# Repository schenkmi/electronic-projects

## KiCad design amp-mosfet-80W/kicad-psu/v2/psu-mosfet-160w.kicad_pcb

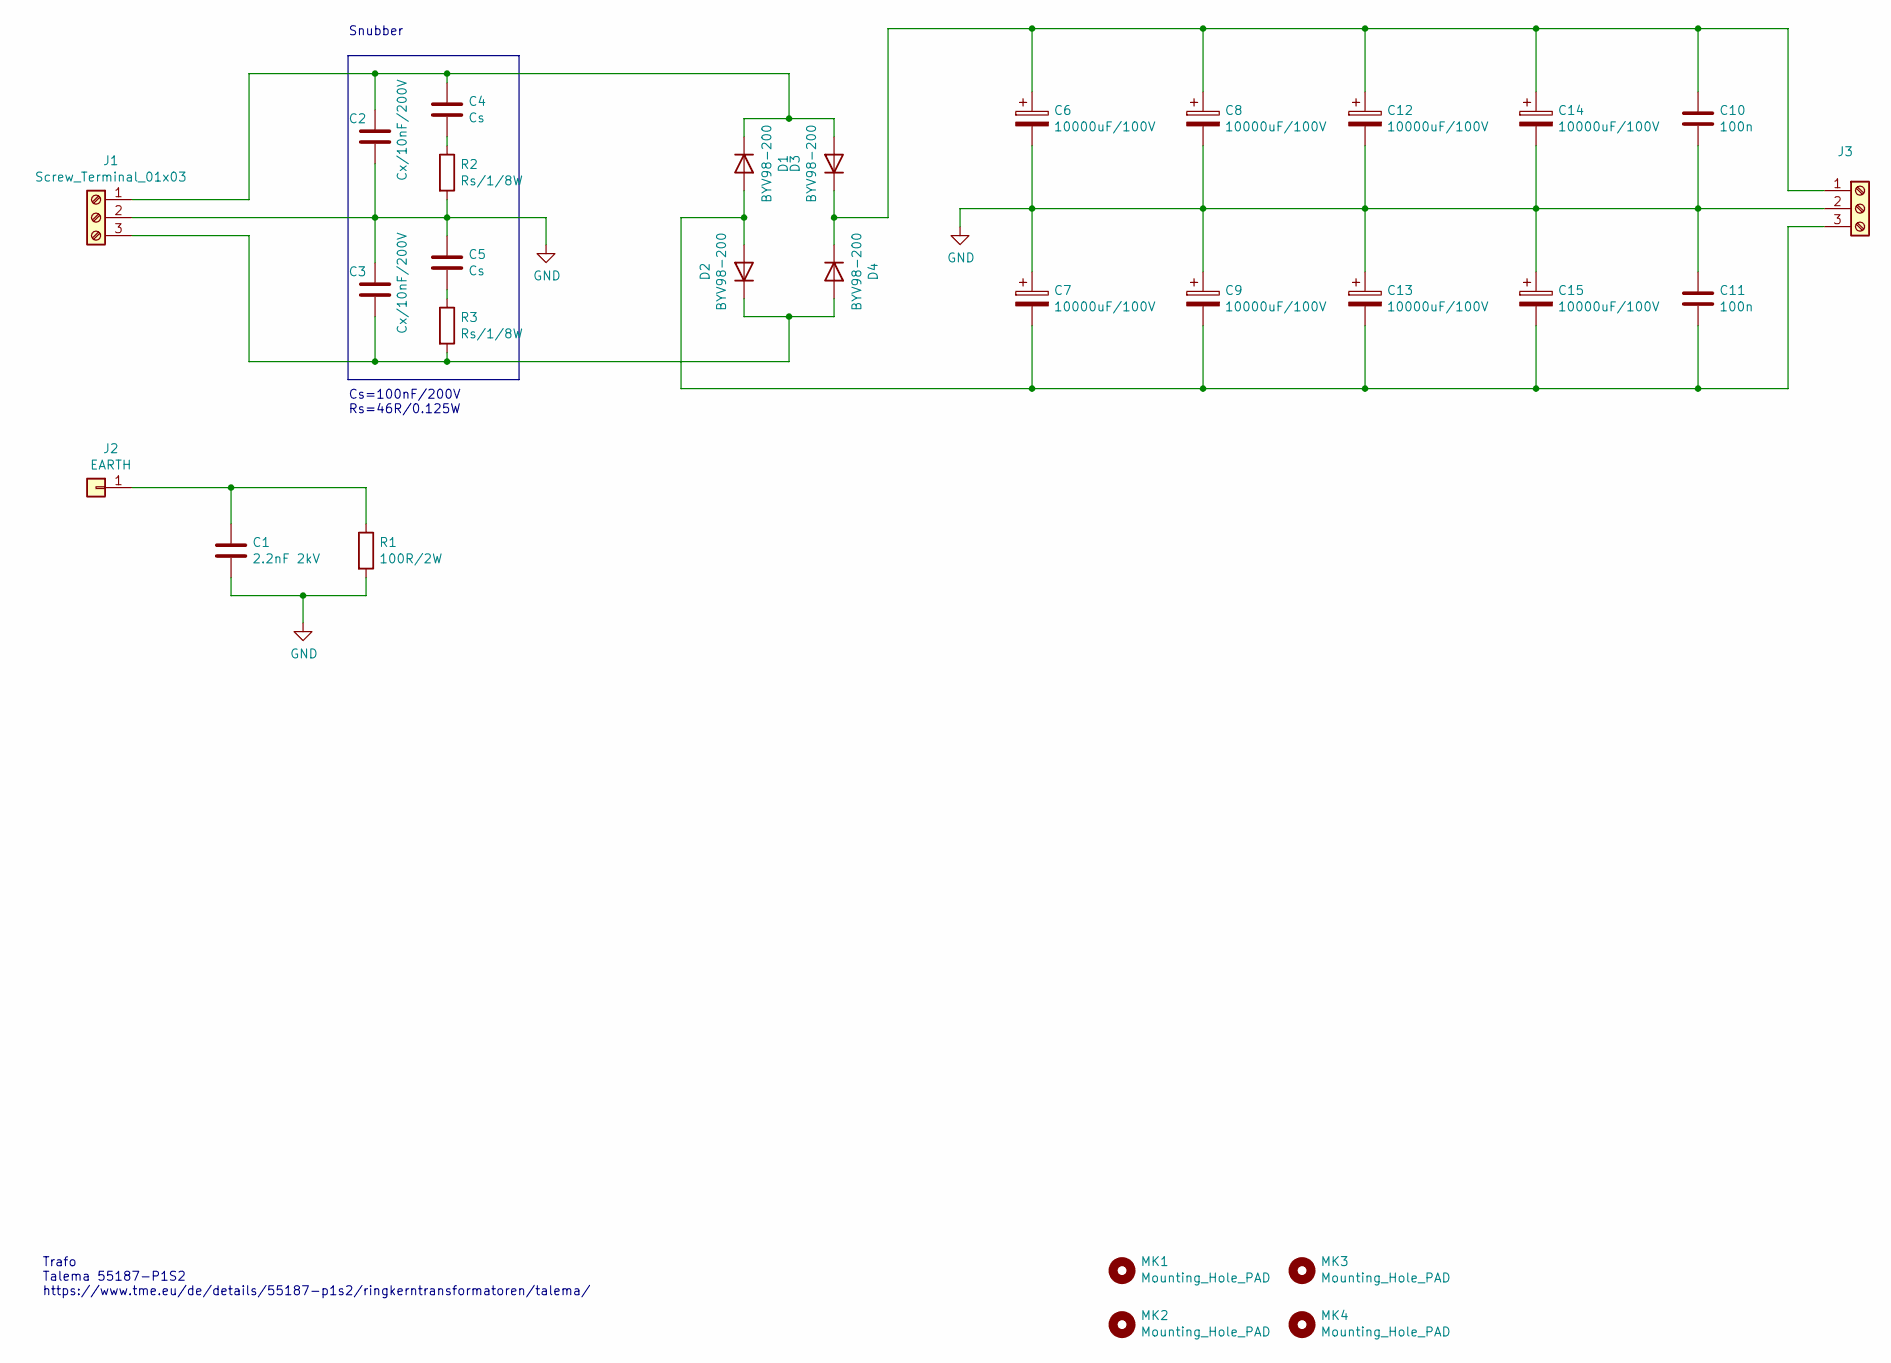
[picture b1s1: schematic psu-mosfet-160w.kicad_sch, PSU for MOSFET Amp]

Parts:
C1: 2.2nF 2kV; C_Rect_L18.0mm_W5.0mm_P15.00mm_FKS3_FKP3
C2, C3: Cx/10nF/200V; C_0805_2012Metric_Pad1.18x1.45mm_HandSolder
C4, C5: Cs; C_1206_3216Metric_Pad1.33x1.80mm_HandSolder
C6, C7, C8, C9, C12, C13, C14, C15: 10000uF/100V; CP_Radial_D40.0mm_P10.00mm_SnapIn
C10, C11: 100n; C_Rect_L7.2mm_W2.5mm_P5.00mm_FKS2_FKP2_MKS2_MKP2
D1, D2, D3, D4: BYV98-200; SOD64-10
J1, J3: Screw_Terminal_01x03; TerminalBlock_RND_205-00013_1x03_P5.00mm_Horizontal
J2: EARTH; Pin_D1.3mm_L11.0mm
MK1, MK2, MK3, MK4: Mounting_Hole_PAD; MountingHole_3.2mm_M3
R1: 100R/2W; R_Axial_DIN0414_L11.9mm_D4.5mm_P15.24mm_Horizontal
R2, R3: Rs/1/8W; R_0805_2012Metric_Pad1.20x1.40mm_HandSolder

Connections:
GND: C1.2, C2.2, C3.1, C5.1, C6.2, C7.1, C8.2, C9.1, C10.2, C11.1, C12.2, C13.1, C14.2, C15.1, J1.2, J3.2, R1.2, R2.2
unnamed: C1.1, J2.1, R1.1
unnamed: C2.1, C4.1, D1.1 (K), D3.2 (A), J1.1
unnamed: C3.2, D2.1 (K), D4.2 (A), J1.3, R3.2
unnamed: C4.2, R2.1
unnamed: C5.2, R3.1
unnamed: C6.1, C8.1, C10.1, C12.1, C14.1, D3.1 (K), D4.1 (K), J3.1
unnamed: C7.2, C9.2, C11.2, C13.2, C15.2, D1.2 (A), D2.2 (A), J3.3

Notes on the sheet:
Snubber
Trafo Talema 55187-P1S2 https://www.tme.eu/de/details/55187-p1s2/ringkerntransformatoren/talema/
Cs=100nF/200V Rs=46R/0.125W

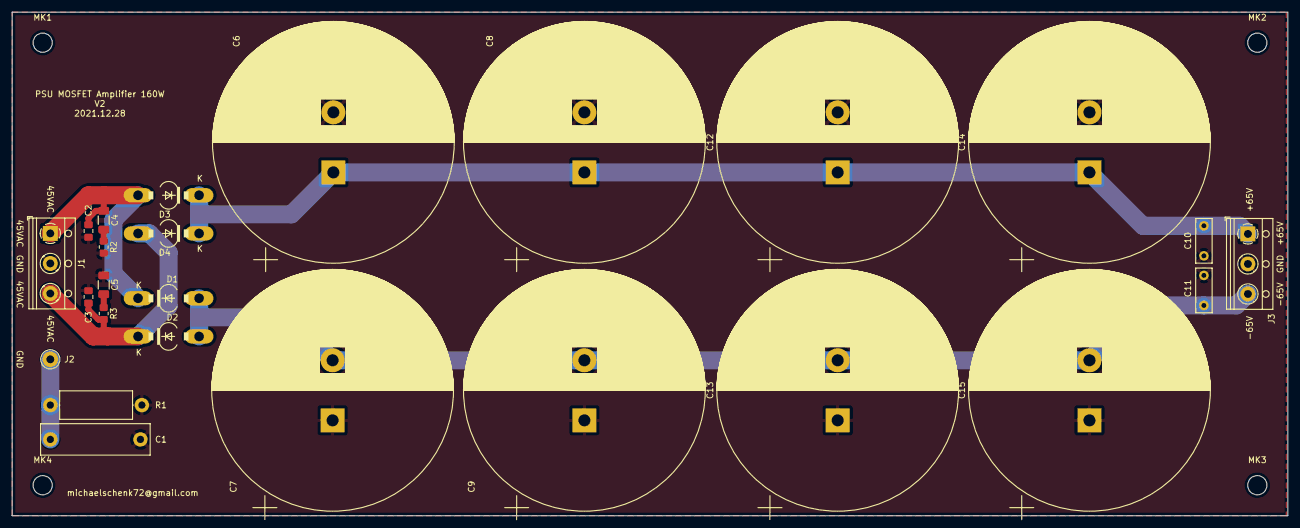
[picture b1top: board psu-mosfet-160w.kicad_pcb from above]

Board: 2 copper layers, 212.3 x 83.8 mm, 29 parts (0 on the bottom side), 8 nets.

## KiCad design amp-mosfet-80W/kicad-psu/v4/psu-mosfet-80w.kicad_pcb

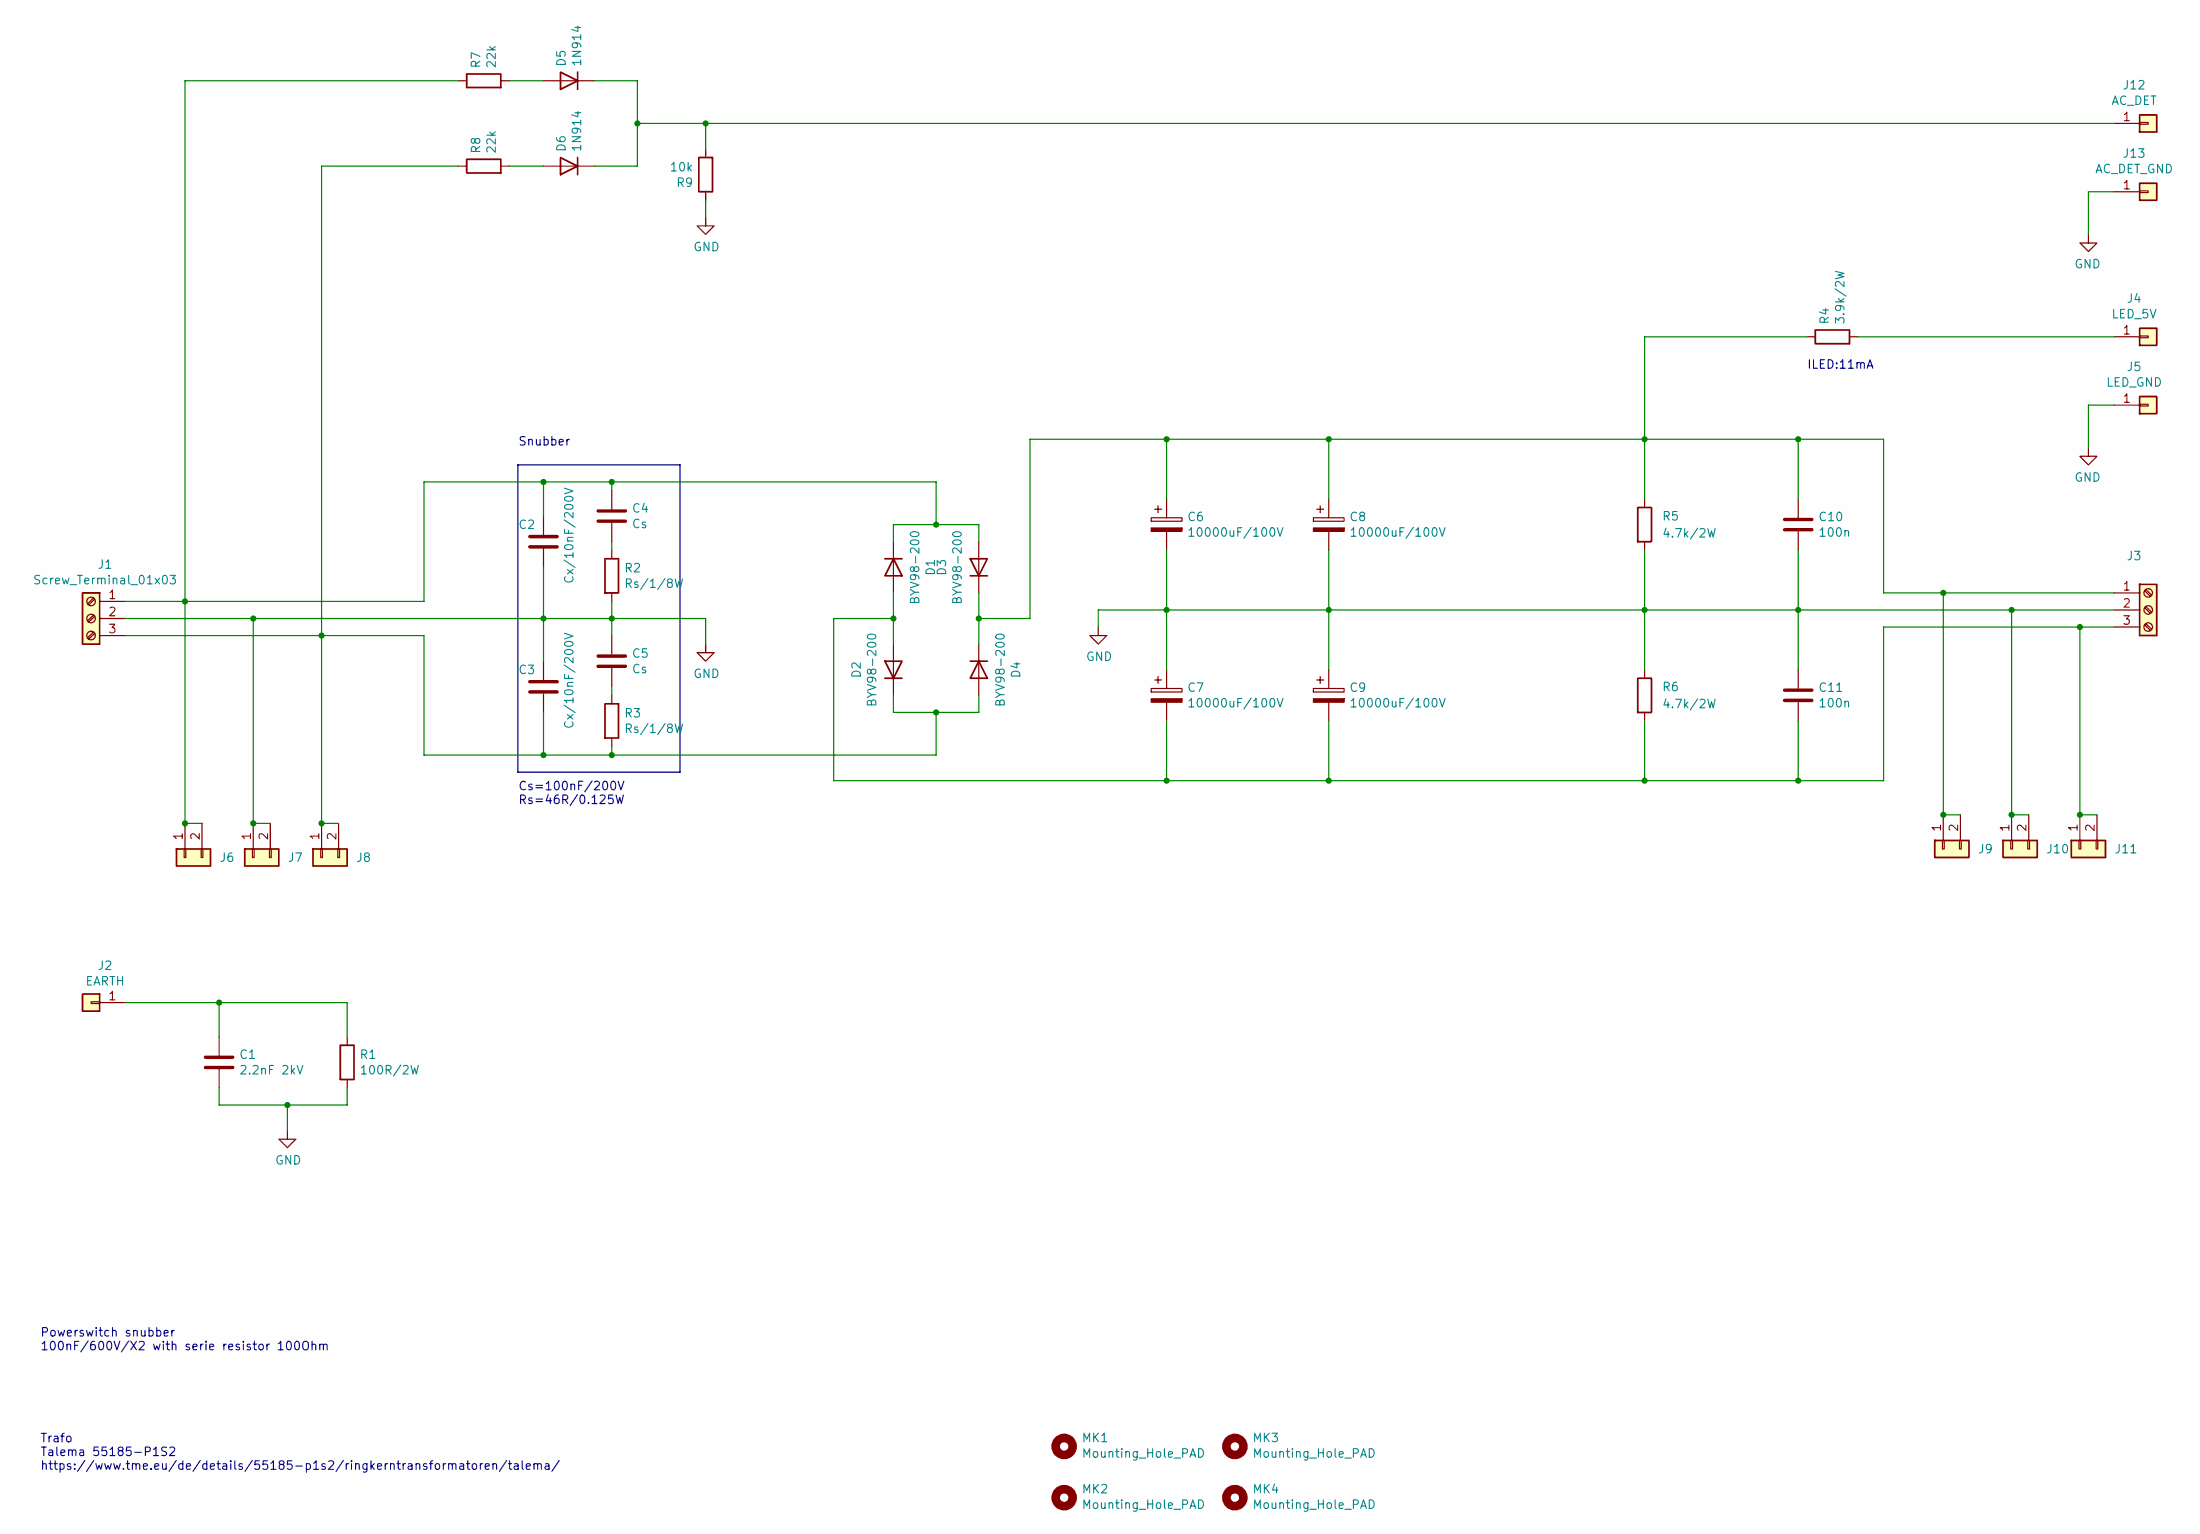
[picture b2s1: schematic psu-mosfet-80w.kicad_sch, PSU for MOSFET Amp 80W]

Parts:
C1: 2.2nF 2kV; C_Rect_L18.0mm_W5.0mm_P15.00mm_FKS3_FKP3
C2, C3: Cx/10nF/200V; C_0805_2012Metric_Pad1.18x1.45mm_HandSolder
C4, C5: Cs; C_1206_3216Metric_Pad1.33x1.80mm_HandSolder
C6, C7, C8, C9: 10000uF/100V; CP_Radial_D40.0mm_P10.00mm_SnapIn
C10, C11: 100n; C_Rect_L7.2mm_W2.5mm_P5.00mm_FKS2_FKP2_MKS2_MKP2
D1, D2, D3, D4: BYV98-200; SOD64-10
D5, D6: 1N914; D_SOD-123
J1, J3: Screw_Terminal_01x03; TerminalBlock_RND_205-00013_1x03_P5.00mm_Horizontal
J2: EARTH; Pin_D1.3mm_L11.0mm
J4: LED_5V; Pin_D1.0mm_L10.0mm
J5: LED_GND; Pin_D1.0mm_L10.0mm
J6, J7, J8, J9, J10, J11: Conn_01x02; TE_62409-1
J12: AC_DET; Pin_D1.0mm_L10.0mm
J13: AC_DET_GND; Pin_D1.0mm_L10.0mm
MK1, MK2, MK3, MK4: Mounting_Hole_PAD; MountingHole_3.2mm_M3
R1: 100R/2W; R_Axial_DIN0414_L11.9mm_D4.5mm_P15.24mm_Horizontal
R2, R3: Rs/1/8W; R_0805_2012Metric_Pad1.20x1.40mm_HandSolder
R4: 3.9k/2W; R_Axial_DIN0414_L11.9mm_D4.5mm_P20.32mm_Horizontal
R5, R6: 4.7k/2W; R_Axial_DIN0414_L11.9mm_D4.5mm_P20.32mm_Horizontal
R7, R8: 22k; R_0805_2012Metric_Pad1.20x1.40mm_HandSolder
R9: 10k; R_0805_2012Metric_Pad1.20x1.40mm_HandSolder

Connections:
GND: C1.2, C2.2, C3.1, C5.1, C6.2, C7.1, C8.2, C9.1, C10.2, C11.1, J1.2, J3.2, J5.1, J7.1, J7.2, J10.1, J10.2, J13.1, R1.2, R2.2, R5.2, R6.1, R9.1
unnamed: C1.1, J2.1, R1.1
unnamed: C2.1, C4.1, D1.1 (K), D3.2 (A), J1.1, J6.1, J6.2, R7.1
unnamed: C3.2, D2.1 (K), D4.2 (A), J1.3, J8.1, J8.2, R3.2, R8.1
unnamed: C4.2, R2.1
unnamed: C5.2, R3.1
unnamed: C6.1, C8.1, C10.1, D3.1 (K), D4.1 (K), J3.1, J9.1, J9.2, R4.1, R5.1
unnamed: C7.2, C9.2, C11.2, D1.2 (A), D2.2 (A), J3.3, J11.1, J11.2, R6.2
unnamed: D5.1 (K), D6.1 (K), J12.1, R9.2
unnamed: D5.2 (A), R7.2
unnamed: D6.2 (A), R8.2
unnamed: J4.1, R4.2

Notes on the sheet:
ILED:11mA
Snubber
Trafo Talema 55185-P1S2 https://www.tme.eu/de/details/55185-p1s2/ringkerntransformatoren/talema/
Powerswitch snubber 100nF/600V/X2 with serie resistor 100Ohm
Cs=100nF/200V Rs=46R/0.125W

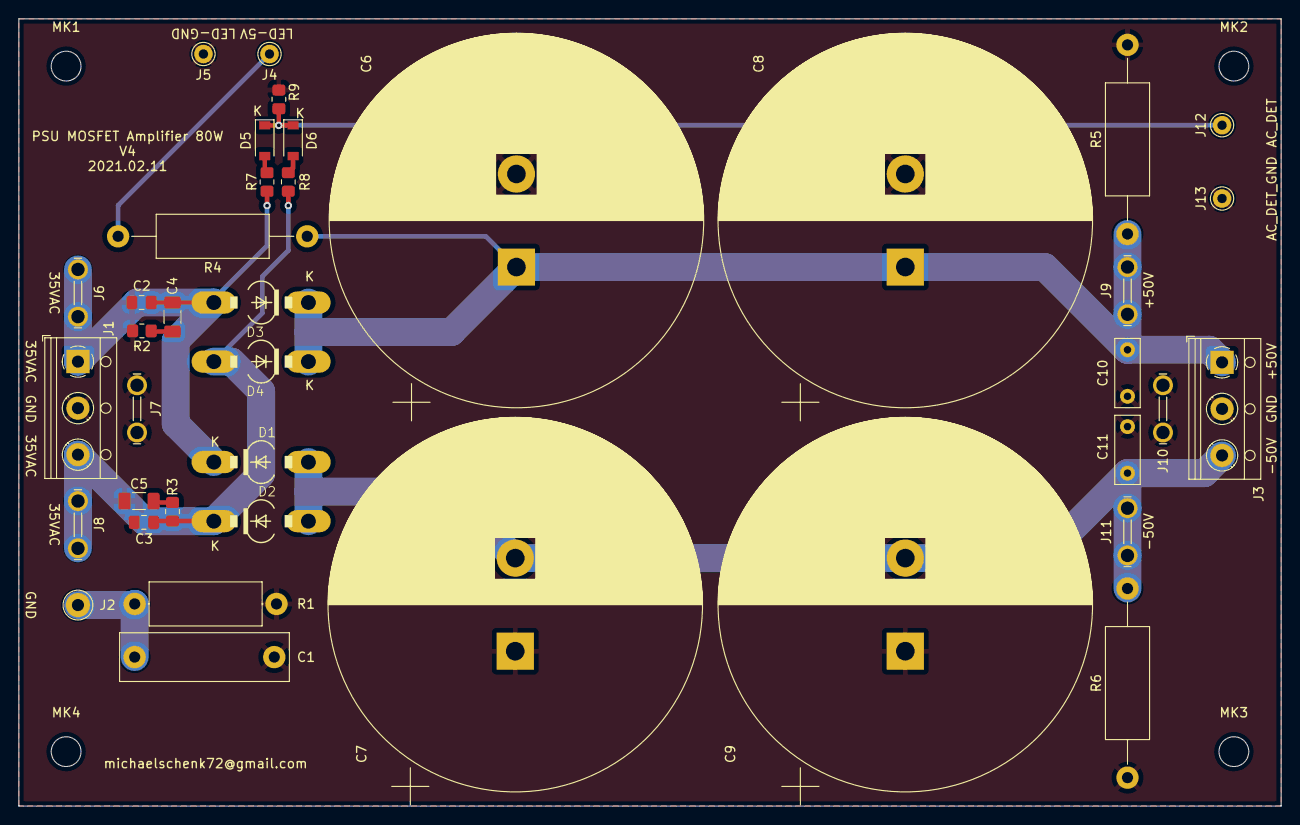
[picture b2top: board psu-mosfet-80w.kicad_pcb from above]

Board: 2 copper layers, 135.6 x 84.6 mm, 43 parts (0 on the bottom side), 12 nets.

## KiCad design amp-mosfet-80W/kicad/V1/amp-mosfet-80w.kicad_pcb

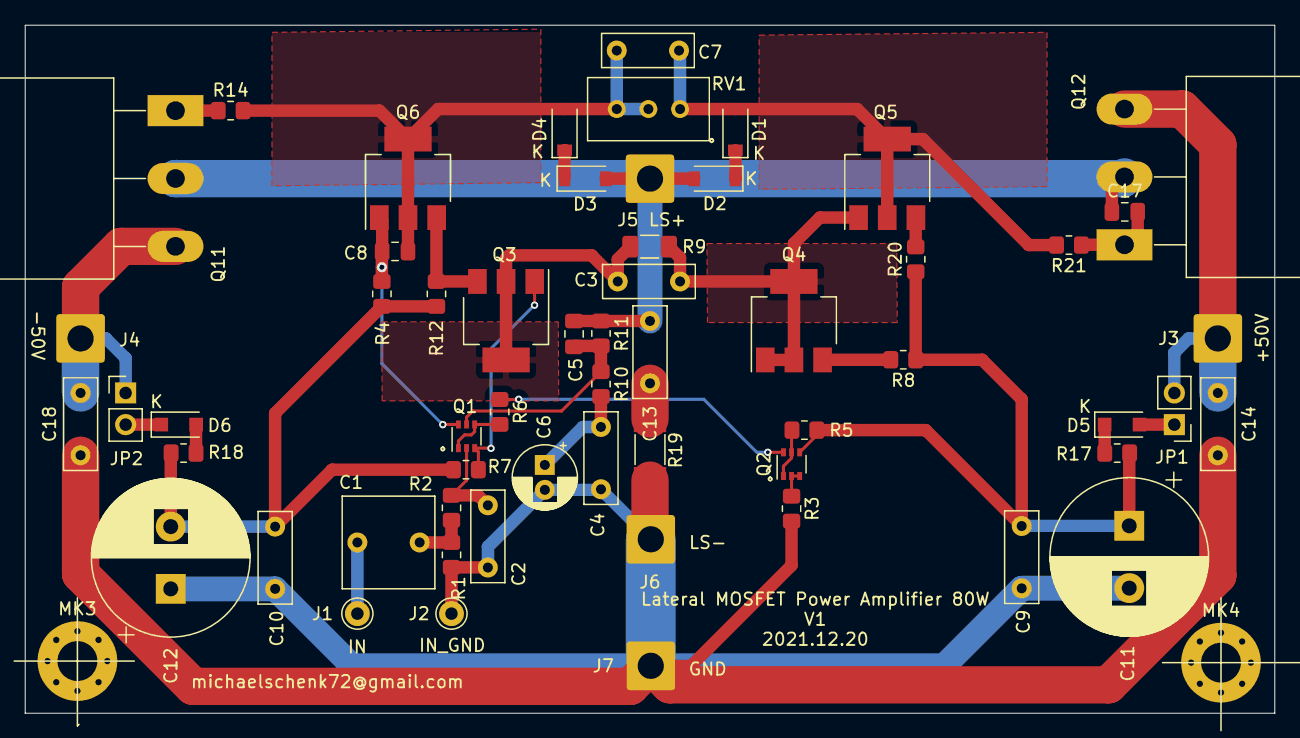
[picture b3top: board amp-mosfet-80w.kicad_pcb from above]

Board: 2 copper layers, 100.3 x 55.2 mm, 60 parts (0 on the bottom side), 33 nets.

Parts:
C1: 2.2uF; C_Rect_L7.2mm_W7.2mm_P5.00mm_FKS2_FKP2_MKS2_MKP2
C2: 1n; C_Rect_L7.2mm_W2.5mm_P5.00mm_FKS2_FKP2_MKS2_MKP2
C3: 10n; C_Rect_L7.2mm_W2.5mm_P5.00mm_FKS2_FKP2_MKS2_MKP2
C4: 47u/16V; CP_Radial_D5.0mm_P2.00mm
C5: 10p; C_0805_2012Metric_Pad1.18x1.45mm_HandSolder
C6, C7, C9, C10, C14, C18: 100n; C_Rect_L7.2mm_W2.5mm_P5.00mm_FKS2_FKP2_MKS2_MKP2
C8: 18p; C_0805_2012Metric_Pad1.18x1.45mm_HandSolder
C11, C12: 220u/100V; CP_Radial_D12.5mm_P5.00mm
C13: 22n; C_Rect_L7.2mm_W2.5mm_P5.00mm_FKS2_FKP2_MKS2_MKP2
C17: 470p; C_0805_2012Metric_Pad1.18x1.45mm_HandSolder
D1, D3: 1N914; D_SOD-123
D2, D4: 12V/0.5W; D_SOD-123
D5, D6: SM4002PL-TP; D_SOD-123F
J1, J2: Conn_01x01; Pin_D1.0mm_L10.0mm
J3: +50V; SolderWire-1.5sqmm_1x01_D1.7mm_OD3.9mm
J4: -50V; SolderWire-1.5sqmm_1x01_D1.7mm_OD3.9mm
J5: LS+; SolderWire-1.5sqmm_1x01_D1.7mm_OD3.9mm
J6: LS-; SolderWire-1.5sqmm_1x01_D1.7mm_OD3.9mm
J7: GND; SolderWire-1.5sqmm_1x01_D1.7mm_OD3.9mm
JP1, JP2: Jump; PinHeader_1x02_P2.54mm_Vertical
MK3, MK4: Mounting_Hole_PAD; MountingHole_3.2mm_M3_Pad_Via
Q1, Q2: BC856BS; SOT-363_SC-70-6
Q3, Q6: DZT5551; SOT-223-3_TabPin2
Q4, Q5: DZT5401; SOT-223-3_TabPin2
Q11: ECX10P20; TO-247-3_Horizontal_TabUp
Q12: ECX10N20; TO-247-3_Horizontal_TabUp
R1, R11: 33k; R_0805_2012Metric_Pad1.20x1.40mm_HandSolder
R2, R10: 1k; R_0805_2012Metric_Pad1.20x1.40mm_HandSolder
R3, R6: 22k; R_0805_2012Metric_Pad1.20x1.40mm_HandSolder
R4, R7: 3k9; R_0805_2012Metric_Pad1.20x1.40mm_HandSolder
R5: 680R; R_0805_2012Metric_Pad1.20x1.40mm_HandSolder
R8, R12, R17, R18, R20: 100R; R_0805_2012Metric_Pad1.20x1.40mm_HandSolder
R9: 12k/1W; R_1206_3216Metric_Pad1.30x1.75mm_HandSolder
R14, R21: 220R; R_0805_2012Metric_Pad1.20x1.40mm_HandSolder
R19: 6.8R/1W; R_MELF_MMB-0207
RV1: 200R; Potentiometer_Bourns_3296W_Vertical

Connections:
GND: C2.2, C4.2, C6.2, C9.2, C10.1, C11.2, C12.1, C14.2, C18.1, J2.1, J6.1, J7.1, R1.2, R3.2, R19.2
unnamed: C1.1, R1.1, R2.2
unnamed: C1.2, J1.1
unnamed: C2.1, Q1.2, R2.1
unnamed: C3.1, Q4.1, Q4.2, Q5.1, R9.1
unnamed: C3.2, Q3.2, R9.2
unnamed: C4.1, C6.1, R10.2
unnamed: C5.2, Q1.5, R10.1, R11.2
unnamed: C7.1, C8.2, D4.2, Q6.2, R14.2, RV1.2, RV1.3
unnamed: C7.2, D1.2, Q5.2, R21.2, RV1.1
unnamed: C8.1, Q1.6, Q6.1, R4.1
unnamed: C10.2, C12.2, R4.2, R7.2, R12.2, R18.2
unnamed: C9.1, C11.1, Q2.4, R5.1, R8.1, R17.1, R20.1
unnamed: C5.1, C13.1, C17.1, D2.2, D3.2, J5.1, Q11.2, Q12.2, R11.1
unnamed: C13.2, R19.1
unnamed: C14.1, J3.1, JP1.2, Q12.3
unnamed: C17.2, Q12.1, R21.1
unnamed: C18.2, J4.1, JP2.1, Q11.3
unnamed: D1.1, D2.1
unnamed: D3.1, D4.1
unnamed: D5.1, R17.2
unnamed: D5.2, JP1.1
unnamed: D6.1, JP2.2
unnamed: D6.2, R18.1
unnamed: Q1.1, Q1.4, R6.2
unnamed: Q1.3, Q3.1, R7.1
unnamed: Q2.1, Q2.5, R5.2
unnamed: Q2.2, Q2.3, R3.1
unnamed: Q2.6, R6.1
unnamed: Q3.3, Q6.3, R12.1
unnamed: Q4.3, R8.2
unnamed: Q5.3, R20.2
unnamed: Q11.1, R14.1
